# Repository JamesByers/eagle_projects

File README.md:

# eagle_projects
This repo contains my Eagle files for various projects

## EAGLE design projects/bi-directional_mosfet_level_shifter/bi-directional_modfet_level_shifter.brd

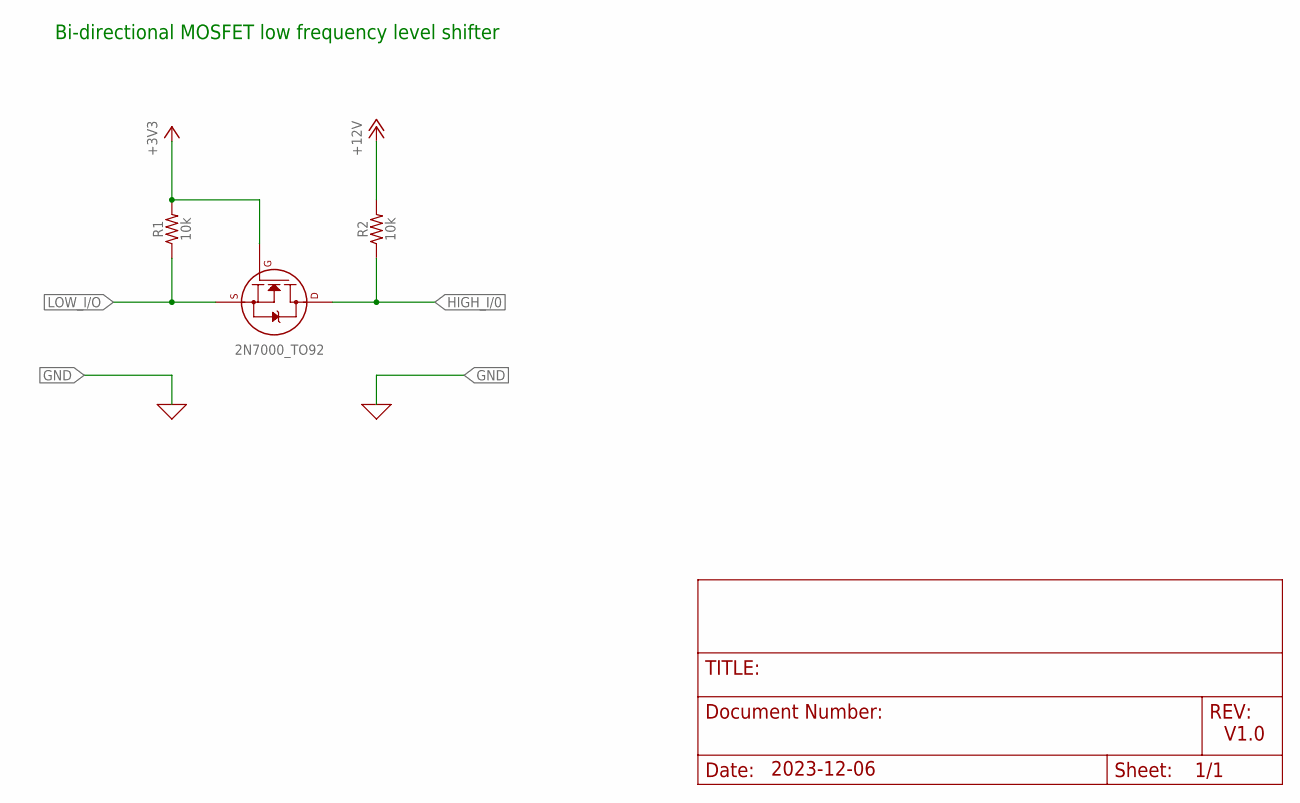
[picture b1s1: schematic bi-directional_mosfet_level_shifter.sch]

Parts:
2N7000_TO92: 2N7000_TO92; TO-92
R1, R2: 10k; AXIAL-0.3-KIT

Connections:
+3V3: 2N7000_TO92.2 (G), R1.P$2 (2)
+12V: R2.P$2 (2)
HIGH_I/0: 2N7000_TO92.3 (D), R2.P$1 (1)
LOW_I/O: 2N7000_TO92.1 (S), R1.P$1 (1)

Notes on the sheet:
Bi-directional MOSFET low frequency level shifter
V1.0
2023-12-06

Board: 2 copper layers, 3 parts (0 on the bottom side), 3 nets, no tracks yet.

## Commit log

2023-12-06 initial files
2023-12-06 initial Kicad files

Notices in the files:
parts and their libraries:
SparkFun-Resistors: Licensing: Creative Commons ShareAlike 4.0 International - https://creativecommons.org/licenses/by-sa/4.0
